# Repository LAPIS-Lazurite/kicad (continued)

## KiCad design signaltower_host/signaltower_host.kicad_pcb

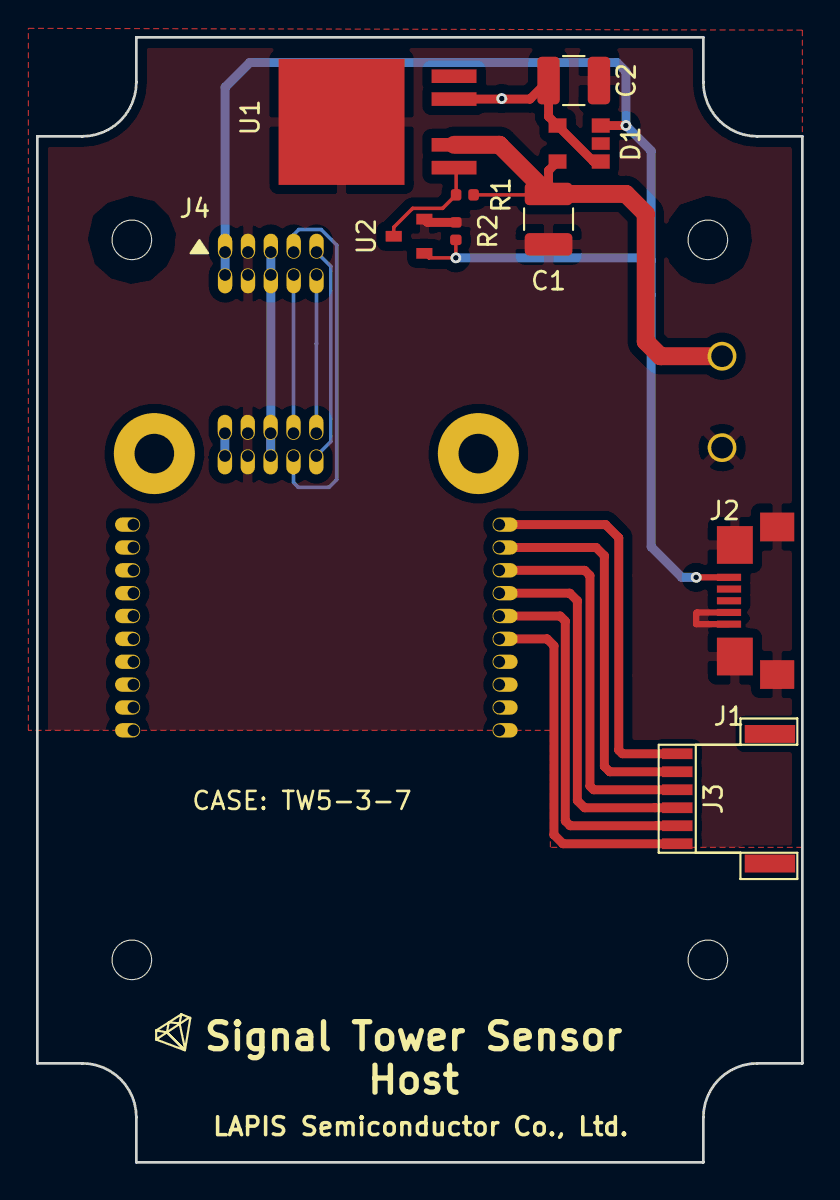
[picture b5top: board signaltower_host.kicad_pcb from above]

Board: 2 copper layers, 42.5 x 62.5 mm, 16 parts (0 on the bottom side), 16 nets.

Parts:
C1, C2: 10uF/50V; C_1210_3225Metric
D1: Diodex2_RRE04EA4D; Diode_SOT-25T
H1, H2, H3, H4: MountingHole; MountingHole_2.2mm_M2
J1: uUSBconecter_ZX62R-B-5P; USB_B_hirose_ZX62R-B-5P
J2: GB-TB-50LBS-2P; GB-50LBS-2P
J3: Conn_01x06_Female; JST_NSH_SM06B_1mm_Horizonal
J4: PSS-720102-05
R1, R2: 100k; R_0402_1005Metric
U1: BD50C0AWFP; LDO_TO252-5
U2: RK7002BMT-116; ROHM_MOSFET_SOT-23
U3: Lazurite_920J; 920J

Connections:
+3V3: J4.5, J4.6, U3.24, U3.25
+5V: C2.1, D1.1, D1.4, U1.4, U3.20, U3.21
+5VP: D1.3, J1.1, J4.1, J4.2, R2.1, U2.1
+24V: C1.1, D1.5, J2.1, R1.1, U1.2
/0: J4.9, U3.0
/1: J4.10, U3.1
/TEST0: J4.7, U3.27
/TEST1N: J4.8, U3.26
GND: C1.2, C2.2, J1.4, J1.5, J1.6, J2.2, J4.3, J4.4, R2.2, U1.fin, U2.2, U3.22, U3.23
unnamed: J3.1, U3.17
unnamed: J3.2, U3.16
unnamed: J3.3, U3.15
unnamed: J3.4, U3.14
unnamed: J3.5, U3.28
unnamed: J3.6, U3.29
unnamed: R1.2, U1.1, U2.3

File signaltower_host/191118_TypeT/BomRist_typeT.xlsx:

| Part | Value | 正式型格セイシキカタカク | パッケージ | メーカ | 備考ビコウ | 員数インスウ
 | U3 |  | Lazurite_920J | 920J | 廣杉計器ヒロスギケイキ | FSS-71034-10x2,FSS-72034-05x1 | 1
 | U2 |  | RK7002BMT-116 | SOT-23 | 部品支給ブヒンシキュウ |  | 1
 | R1,R2 | 100k |  | R_0402_1005Metric | 指定なしシテイ |  | 2
 | U1 |  | BD3574YFP-ME2 | TO252-5 | 部品支給ブヒンシキュウ |  | 1
 | J4 |  | PSS-720102-05 | PSS-720102-05 | 廣杉計器ヒロスギケイキ |  | 1
 | J3 |  | _5051100892 | _5051100892 | molex | FFC-FPCｺﾈｸﾀ | 1
 | J2 |  | GB-TB-50LBS-2P | GB-50LBS-2P | GB | 小型ターミナルブロックコガタ | 1
 | J1 |  | ZX62R-B-5P | ZX62R-B-5P | ヒロセ |  | 1
 | D1 |  | RRE04EA4D | SOT-25T | 部品支給ブヒンシキュウ |  | 1
 | C2,C1 | 10uF/50V |  | C_1210_3225Metric | 指定なしシテイ |  | 2

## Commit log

2020-05-20 first upload
2020-06-12 update signal sensor host/slave
2020-07-01 signal_sensor-host signal_sensor-slave サイズを小型化 コネクタを変更
2020-07-22 signal tower sensor host/slave updated.
2020-12-09 sync 20201209
2021-02-27 finish design of CTSensor3
